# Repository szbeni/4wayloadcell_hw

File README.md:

# 4wayloadcell_hw
4wayloadcell_hw

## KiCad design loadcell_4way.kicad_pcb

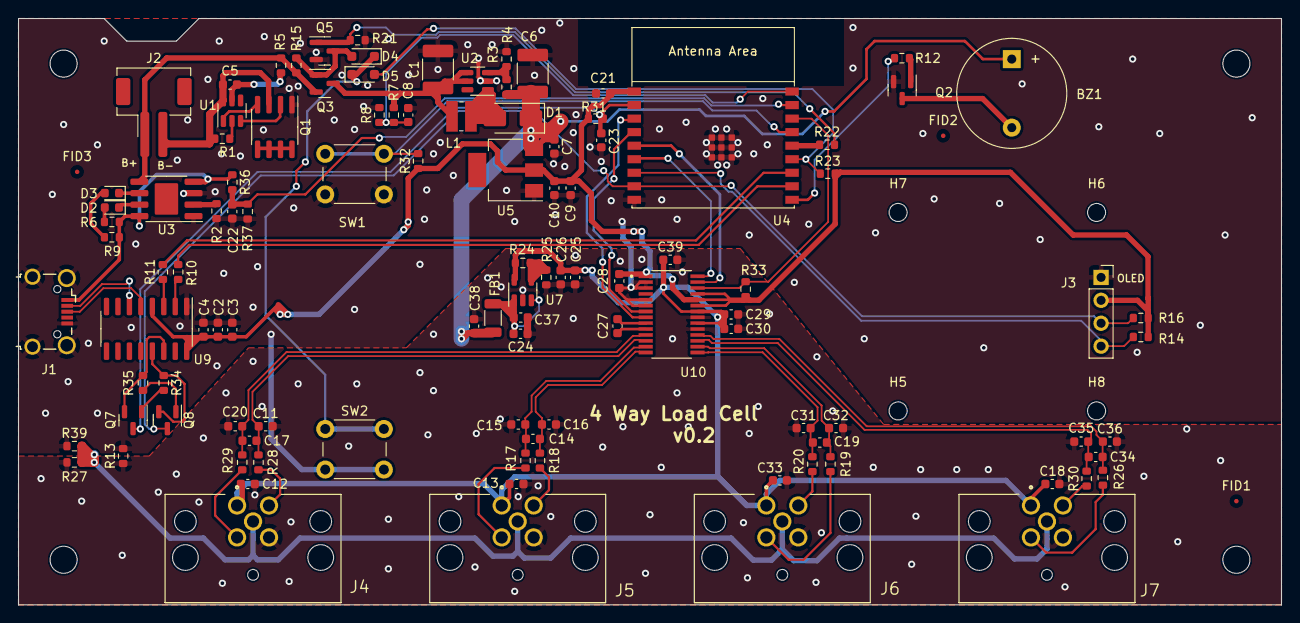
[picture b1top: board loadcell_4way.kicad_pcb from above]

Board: 2 copper layers, 140.0 x 65.0 mm, 119 parts (0 on the bottom side), 71 nets.

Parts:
BZ1: Buzzer; Buzzer_12x9.5RM7.6
C1, C6: 22uF; C_1812_4532Metric
C2, C7, C9, C23, C24, C25: 10uF; C_0603_1608Metric
C3, C4, C5, C8, C10, C11, C12, C13, C14, C15, C16, C17, C18, C19, C20, C21, C22, C26, C27, C28, C29, C30, C31, C32, C33, C34, C35, C36, C37, C38, C39: 100nF; C_0603_1608Metric
D1: SS34; D_SMA
D2: LED RED; D_0603_1608Metric
D3: LED GREEN; D_0603_1608Metric
D4, D5: 1SS355; D_SOD-323_HandSoldering
FB1: FerriteBead; L_1206_3216Metric
FID1, FID2, FID3: Fiducial; Fiducial_0.5mm_Mask1.5mm
H1, H2, H3, H4: PCB Mounting hole; MountingHole_3mm
H5, H6, H7, H8: MountingHole; MountingHole_2mm_OLED
J1: USB_B_Micro; USB_Micro-B_Wuerth_629105150521_CircularHoles
J2: Battery; JST_PH_B2B-PH-SM4-TB_1x02-1MP_P2.00mm_Vertical_long
J3: OLDED_Screen; PinSocket_1x04_P2.54mm_Vertical
J4, J5, J6, J7: T4145015051-001; TE_T4145015051-001
L1: 22uH; L_Wuerth_MAPI-3012
Q1: FDS9926A; SOIC-8_3.9x4.9mm_P1.27mm
Q2, Q5, Q7, Q8: BSS138; SOT-23
Q3: SM2331PSA P-MOSFET; SOT-23
R1, R2: 2k; R_0603_1608Metric
R3: 7.5k; R_0603_1608Metric
R4, R6, R9, R17, R18, R19, R20, R26, R28, R29, R30: 1k; R_0603_1608Metric
R5, R12, R22: 100; R_0603_1608Metric
R7, R36: 390k; R_0603_1608Metric
R8, R15, R23, R37: 100k; R_0603_1608Metric
R10, R11: 470R; R_0603_1608Metric
R13, R27, R39: 0R; R_0603_1608Metric
R14, R16: 4k7; R_0603_1608Metric
R21, R24, R31, R32, R33, R34, R35: 10k; R_0603_1608Metric
R25: 2k2; R_0603_1608Metric
SW1, SW2: SW_Push; SW_PUSH_6mm
U1: FS312F-G; SOT-23-6
U2: MT3608; SOT-23-6
U3: TP4056; SOP8-PP
U4: ESP32-C3-WROOM-02
U5: LM1117-3.3; SOT-223
U7: AP2127K-ADJ; SOT-23-5
U9: CH340C; SOIC-16_3.9x9.9mm_P1.27mm
U10: ADS1234IPW; SOP65P640X120-28N

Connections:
+3V3: C2.1, C3.1, C4.1, C9.1, C10.1, C21.1, C28.1, J3.2, R14.2, R16.2, R23.2, R31.1, R32.1, R33.1, U4.1 (3V3), U5.2 (VO), U9.4 (V3), U9.16 (VCC), U10.1 (DVDD), U10.23 (GAIN0), U10.24 (GAIN1), U10.25 (SPEED)
+5V: BZ1.1 (-), C6.1, C7.1, C38.1, D1.1 (K), FB1.1, R3.2, U5.3 (VI)
A1+: C17.1, C20.1, R29.2, U10.11 (AINP1)
A1-: C11.1, C17.2, R28.2, U10.12 (AINN1)
A2+: C14.1, C16.1, R17.2, U10.13 (AINP3)
A2-: C14.2, C15.1, R18.2, U10.14 (AINN3)
A3+: C19.1, C32.1, R19.2, U10.16 (AINP4)
A3-: C19.2, C31.1, R20.2, U10.15 (AINN4)
A4+: C34.1, C36.1, R26.2, U10.18 (AINP2)
A4-: C34.2, C35.1, R30.2, U10.17 (AINN2)
BAT+: J2.1, Q3.2 (S), R5.1, R15.2, U3.5 (BAT)
BAT-: C5.2, J2.2, Q1.3 (S2), R1.2, U1.6 (GND)
BTN_1: R32.2, SW1.1, U4.15 (GPIO3/ADC1_CH3)
BTN_2: D5.2 (A), R23.1, U4.13 (GPIO18/USB_D-)
BUZZER: R12.2, U4.10 (GPIO10)
CLK: U4.5 (GPIO6), U10.27 (SCLK)
D+: J1.3 (D+), U9.5 (UD+)
D-: J1.2 (D-), U9.6 (UD-)
DOUT: U4.6 (GPIO7), U10.28 (~DRDY~{/DOUT)
ESP32_EN: C23.1, Q7.3 (D), R31.2, U4.2 (EN/CHIP_PU)
ESP32_IO9: J3.3, Q8.3 (D), R16.1, U4.8 (GPIO9)
GND: C1.2, C2.2, C3.2, C4.2, C6.2, C7.2, C8.2, C9.2, C10.2, C21.2, C22.2, C23.2, C28.2, J1.5 (GND), J1.6 (Shield), J3.1, Q1.1 (S1), Q2.2 (S), Q5.2 (S), R2.2, R4.1, R8.2, R13.2, R21.1, R37.2, R39.1, SW1.2, SW2.2, U2.2 (GND), U3.1 (TEMP), U3.3 (GND), U4.9 (GND), U4.19 (GND), U5.1 (GND), U9.1 (GND), U10.2 (DGND), U10.3 (CLKIN/XTAL1), U10.5 (DGND), U10.6 (DGND)
GNDA: C11.2, C12.2, C13.2, C15.2, C16.2, C18.2, C20.2, C24.2, C25.2, C26.2, C29.2, C30.2, C31.2, C32.2, C33.2, C35.2, C36.2, C37.2, C38.2, C39.2, J4.3, J5.3, J6.3, J7.3, R13.1, R25.1, R27.1, U7.2 (GND), U10.19 (REFN), U10.21 (AGND)
MUX0: U4.3 (GPIO4/ADC1_CH4), U10.8 (A0)
MUX1: U4.4 (GPIO5/ADC2_CH0), U10.7 (A1)
unnamed: BZ1.2 (+), Q2.3 (D)
unnamed: D1.2 (A), L1.2, U2.1 (SW)
unnamed: D2.2 (A), R6.1
unnamed: D2.1 (K), U3.7 (CHRG)
unnamed: D3.2 (A), R9.1
unnamed: D3.1 (K), U3.6 (STDBY)
unnamed: D4.2 (A), Q3.1 (G), Q5.3 (D), R15.1
unnamed: D4.1 (K), D5.1 (K), SW2.1
unnamed: J4.2, R28.1
unnamed: J4.4, R29.1
unnamed: J5.2, R18.1
unnamed: J5.4, R17.1
unnamed: J6.2, R20.1
unnamed: J6.4, R19.1
unnamed: J7.2, R30.1
unnamed: J7.4, R26.1
unnamed: Q1.5 (D2), Q1.6 (D2), Q1.7 (D1), Q1.8 (D1)
unnamed: Q1.2 (G1), U1.3 (OC)
unnamed: Q1.4 (G2), U1.1 (OD)
unnamed: Q2.1 (G), R12.1
unnamed: Q5.1 (G), R21.2, R22.2
unnamed: Q7.1 (G), R34.2
unnamed: Q7.2 (S), R35.1, U9.14 (~RTS)
unnamed: Q8.1 (G), R35.2
unnamed: Q8.2 (S), R34.1, U9.13 (~DTR)
unnamed: R1.1, U1.2 (CS)
unnamed: C5.1, R5.2, U1.5 (VCC)
unnamed: R3.1, R4.2, U2.3 (FB)
unnamed: R2.1, U3.2 (PROG)
unnamed: R24.1, R25.2, U7.4 (ADJ)
unnamed: C24.1, C37.1, FB1.2, U7.1 (VIN), U7.3 (EN)
unnamed: R11.1, U9.3 (RXD)
unnamed: R10.1, U9.2 (TXD)
unnamed: C27.1, U10.9 (CAP_1)
unnamed: C27.2, U10.10 (CAP_2)
PWDN: R33.2, U4.16 (GPIO2/ADC1_CH2), U10.26 (~PDWN)
PWR_EN: R22.1, U4.14 (GPIO19/USB_D+)
RXD: R10.2, U4.11 (GPIO20/U0RXD)
SDA: J3.4, R14.1, U4.7 (GPIO8)
SHIELD: J4.5, J5.5, J6.5, J7.5, R27.2, R39.2
TXD: R11.2, U4.12 (GPIO21/U0TXD)
VBAT_FB: C8.1, R7.2, R8.1, U4.18 (GPIO0/ADC1_CH0/XTAL_32K_P)
VBUS: J1.1 (VBUS), R6.2, R9.2, R36.1, U3.4 (VCC), U3.8 (CE)
VBUS_FB: C22.1, R36.2, R37.1, U4.17 (GPIO1/ADC1_CH1/XTAL_32K_N)
VCC: C1.1, L1.1, Q3.3 (D), R7.1, U2.4 (EN), U2.5 (IN)
VDDA: C12.1, C13.1, C18.1, C25.1, C26.1, C29.1, C30.1, C33.1, C39.1, J4.1, J5.1, J6.1, J7.1, R24.2, U7.5 (VOUT), U10.20 (REFP), U10.22 (AVDD)

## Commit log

2023-06-08 initial
2023-06-08 esp32-c3 ch340c
2023-06-14 pcb wip
2023-07-04 added enclusre fixed lcd spin around and button
2023-07-08 encosure wip
2023-07-08 v0.2 wip
2023-07-13 v0.2
